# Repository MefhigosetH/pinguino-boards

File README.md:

pinguino-boards
===============

Personal Pinguino-project OpenHardware schematics and boards.

For more info, please visit:

* Official site at http://www.pinguino.cc
* My personal blog at http://www.mefhigoseth.com.ar/p/pinguino.html

Notes:

* The schematics and boards are designed with Kicad 2012-nov-02 version.
* Master branch have the latest stable board design. Recomended for production. Test passed.
* Testing branch may have partial, incomplete or non-functional boards. Use at your own risk.

# pinguino-2550-v1

Pinguino board based on PIC18F2550. Features:

* Small form factor: 80x30 mm
* External power supply bornier.
* LM7805 1Amp 5v Positive voltaje regulator with 5-18v input.
* USB Self-powered or external swith, via jumper.
* Power (red) and User (green) 5mm led.
* Easy access to all I/O port, including PWM and UART.
* Easy home-based build the board (DIY).

# pinguino-2550-v2

Pinguino board based on PIC18F2550. Features:

* Form factor: 100x50 mm.
* External power supply bornier.
* LM7805 1Amp 5v Positive voltaje regulator with 5-18v input voltaje.
* USB Self-powered or external BATT select jumper.
* Power (red) and User (green) 3mm led.
* Easy access to all I/O port including PWM and UART, via 8A borniers.
* Easy home-based build the board (DIY).

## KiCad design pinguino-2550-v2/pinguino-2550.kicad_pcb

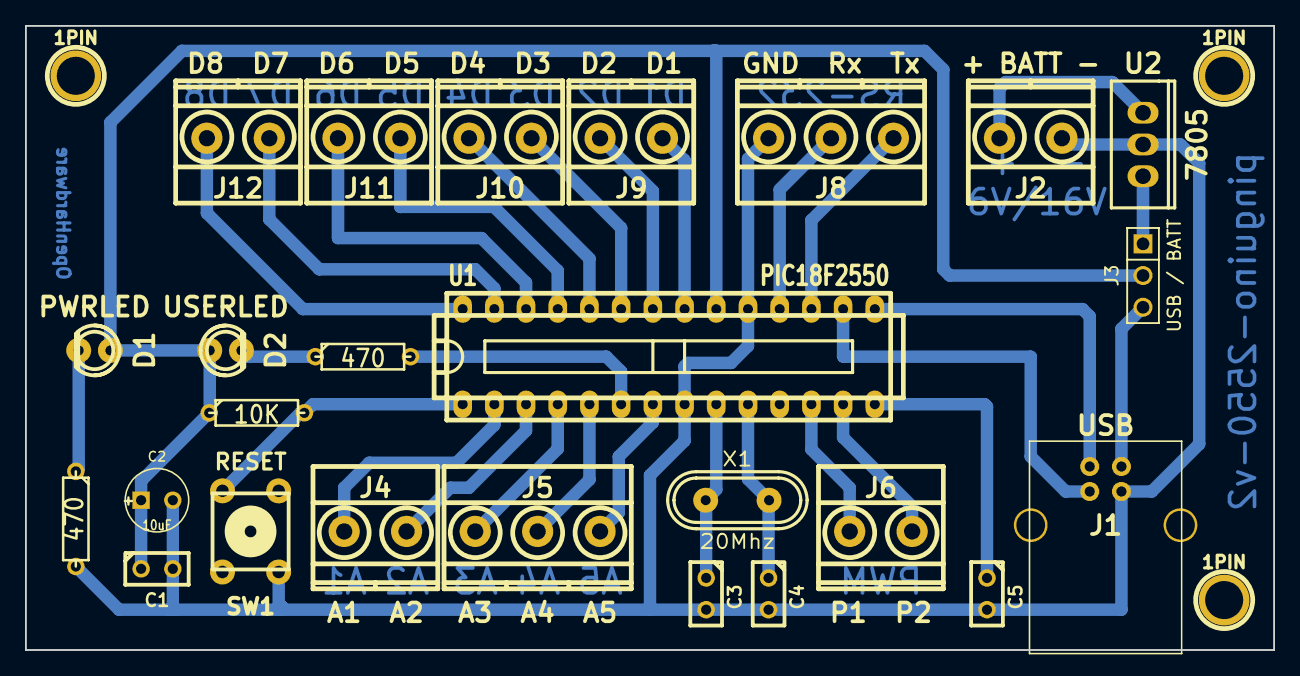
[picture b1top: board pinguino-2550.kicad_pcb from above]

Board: 2 copper layers, 100.0 x 50.0 mm, 28 parts (0 on the bottom side), 31 nets.

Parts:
1PIN, 1PIN#2, 1PIN#3: P***; 1pin
C1: 100nF; C1
C2: 10uF; C1V5
C3, C4: 22pF; C1
C5: 220nF; C1
D1: PWRLED; led_3mm_red
D2: USERLED; led_3mm_green
J1: USB; USB_B
J2: + BATT -; mkds_1,5-2
J3: USB / BATT; PIN_ARRAY_3X1
J4: A1 A2; mkds_1,5-2
J5: A3 A4 A5; mkds_1,5-3
J6: P1 P2; mkds_1,5-2
J8: GND Rx Tx; mkds_1,5-3
J9: D2 D1; mkds_1,5-2
J10: D4 D3; mkds_1,5-2
J11: D6 D5; mkds_1,5-2
J12: D8 D7; mkds_1,5-2
R1, R3: 470; R3
R2: 10K; R3
SW1: RESET; PCB_PUSH
U1: PIC18F2550; dil_28-300_socket
U2: 7805; to220_std
X1: 20Mhz; crystal_hc-49s

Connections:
/ANALOG-1: J4.1, U1.2
/ANALOG-2: J4.2, U1.3
/ANALOG-3: J5.1, U1.4
/ANALOG-4: J5.2, U1.5
/ANALOG-5: J5.3, U1.7
/DIGITAL-1: J9.1, U1.21
/DIGITAL-2: J9.2, U1.22
/DIGITAL-3: J10.1, U1.23
/DIGITAL-4: J10.2, U1.24
/DIGITAL-5: J11.1, U1.25
/DIGITAL-6: J11.2, U1.26
/DIGITAL-7: J12.1, U1.27
/DIGITAL-8: J12.2, U1.28
/PWM-1: J6.1, U1.12
/PWM-2: J6.2, U1.13
/UART-RX: J8.2, U1.18
/UART-TX: J8.1, U1.17
/USB+: J1.3, U1.16
/USB-: J1.2, U1.15
GNDPWR: C1.2, C2.2, C3.2, C4.2, C5.2, J1.4, J2.1, J8.3, R1.2, SW1.1, U1.8, U1.19, U2.2
unnamed: R2.2, SW1.2, U1.1
unnamed: R3.2, U1.6
unnamed: D2.2, R3.1
unnamed: J2.2, U2.1
unnamed: J3.1, U2.3
unnamed: J1.1, J3.3
unnamed: C5.1, U1.14
unnamed: C3.1, U1.9, X1.1
unnamed: C4.1, U1.10, X1.2
unnamed: D1.2, R1.1
VCC: C1.1, C2.1, D1.1, D2.1, J3.2, R2.1, U1.20

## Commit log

2014-02-23 First commit. Updated README file.
2014-02-23 Added pinguino-2550-v1 board
2014-02-23 Updated README file.
2014-04-03 First commit pinguino-2550-v2
2014-04-04 Added BoM. Fixed pcbnew paper size.
2014-08-15 Cupper layer text mirroring.
2014-08-16 Fixed bornier modules text.
2014-08-16 Updated README.md: Added pinguino-2550-v2 board.
2014-08-16 Updated README.md: Added 3D board models.
2014-08-16 Updated README.md: Added notes.
2021-04-24 feat(3d): Updated 3d model for pinguino-2550-v2 board.
